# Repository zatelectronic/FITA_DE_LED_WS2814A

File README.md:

<div align="center">

# WS2814A

**Barra de LEDs endereçáveis RGBW com 10 pixels WS2814C — protocolo de 1 fio, encadeável, totalmente SMD, alimentação 5V**

</div>

---

## 📋 Índice

- [WS2814A](#ws2814a)
  - [📋 Índice](#-índice)
  - [Visão Geral](#visão-geral)
  - [Renders 3D](#renders-3d)
  - [Funcionalidades](#funcionalidades)
  - [Arquitetura do Pixel](#arquitetura-do-pixel)
  - [Especificações Técnicas](#especificações-técnicas)
  - [Lista de Materiais](#lista-de-materiais)
  - [Pinagem dos Conectores](#pinagem-dos-conectores)
    - [J1 — Entrada (lado esquerdo)](#j1--entrada-lado-esquerdo)
    - [J2 — Saída (lado direito)](#j2--saída-lado-direito)
  - [Encadeamento de Barras](#encadeamento-de-barras)
  - [Aplicações](#aplicações)
  - [Estrutura do Repositório](#estrutura-do-repositório)
  - [Como Usar](#como-usar)
    - [Conexão básica com Arduino / ESP32](#conexão-básica-com-arduino--esp32)
    - [Exemplo com Adafruit NeoPixel](#exemplo-com-adafruit-neopixel)
  - [Sobre](#sobre)

---

## Visão Geral

**WS2814A** é uma barra de LEDs endereçáveis **RGBW** com **10 pixels** individuais, projetada pela **ZAT ELECTRONIC** utilizando **KiCad 10**. Cada pixel é composto por um controlador **WS2814C** (SMD) e um LED **QBLP679-RGBCW** (RGBW — 4 canais: Vermelho, Verde, Azul e Branco), permitindo controle independente de cor e intensidade por pixel.

A comunicação utiliza o protocolo **single-wire (1 fio)** compatível com a família WS28xx, suportado por bibliotecas com modo RGBW, como a **Adafruit NeoPixel**. A barra possui conector de **entrada (DIN)** e **saída (DOUT)** em ambas as extremidades, permitindo **encadeamento de múltiplas barras** em série com um único pino de dados do microcontrolador.

> 💡 O canal **branco dedicado (W)** do LED QBLP679-RGBCW proporciona iluminação branca de alta qualidade sem mistura de cores RGB, ideal para aplicações de iluminação ambiente e fotografia.

---

## Renders 3D

<div align="center">

*Vista superior — 10 pixels RGBW em série, controladores WS2814C e capacitores de desacoplamento*

<br/>

*Vista isométrica — layout compacto SMD com conectores de entrada e saída nas extremidades*

</div>

---

## Funcionalidades

- ✅ **10 pixels RGBW endereçáveis** — controle individual de cor e brilho por pixel
- ✅ **Controlador WS2814C** (SMD) por pixel — protocolo single-wire compatível com WS28xx
- ✅ **LED QBLP679-RGBCW** por pixel — RGBW com canal branco dedicado (4 canais)
- ✅ **Protocolo 1 fio** — família WS28xx, quadro de 32 bits por pixel (R, G, B, W); compatível com Adafruit NeoPixel (NEO_RGBW)
- ✅ **Encadeável (DIN → DOUT)** — múltiplas barras em série com 1 único pino de dados
- ✅ **Conector de entrada J1** (5V / DIN / GND) — lado esquerdo da barra
- ✅ **Conector de saída J2** (5V / DOUT / GND) — lado direito para encadeamento
- ✅ **Filtro RC no VDD de cada WS2814C** — R1–R10 100 Ω + C1–C10 100 nF (0603 SMD)
- ✅ **3 pontos fiduciais** (FID1–FID3) — referência para montagem SMD automatizada
- ✅ **Alimentação 5VDC** — compatível com fontes USB e reguladores padrão
- ✅ **Layout totalmente SMD** — compacto e adequado para fabricação automatizada

---

## Arquitetura do Pixel

Cada um dos 10 pixels da barra é composto por:

```
   +5V ──[R_n 100Ω]──┬──► VDD  WS2814C (U_n)            +5V
                     │                                    │
               [C_n 100nF]          OUTR ──► K_R ┐        │
                     │              OUTG ──► K_G │ D_n    ├── anodos A_R / A_G / A_B / A_W
                    GND             OUTB ──► K_B │ RGBW   │
                                    OUTW ──► K_W ┘        │
DIN_n ─────────────────────────────► DIN
                                     DOUT ──► DIN do próximo pixel
```

Os pixels são encadeados internamente em série, do U1/D1 ao U10/D10, com o sinal de dados propagando de pixel em pixel até chegar ao conector de saída DOUT.

---

## Especificações Técnicas

| Parâmetro | Valor |
|-----------|-------|
| **Quantidade de pixels** | 10 |
| **Controlador por pixel** | WS2814C (SMD) |
| **LED por pixel** | QBLP679-RGBCW (RGBW — 4 canais) |
| **Canais de cor** | Vermelho, Verde, Azul, Branco |
| **Resolução por canal** | 8 bits (0–255) por cor |
| **Protocolo de dados** | Single-wire — compatível WS28xx |
| **Tensão de alimentação** | 5VDC (WS2814C: 3,7 V a 5,3 V no VDD) |
| **Corrente por canal** | ~16,5 mA (corrente constante do WS2814C) |
| **Consumo máximo** | ~0,66 A em +5V (10 pixels × 4 canais em 100%) |
| **Conector de entrada** | J1 — 3 pinos: GND / DIN / 5V (pino 1 = GND) |
| **Conector de saída** | J2 — 3 pinos: 5V / DOUT / GND |
| **Capacitores** | 100nF / 0603 SMD (1 por pixel, VDD do WS2814C) |
| **Resistores** | 100Ω / 0603 SMD (1 por pixel, série no VDD do WS2814C) |
| **Fiduciais** | 3x (FID1, FID2, FID3) |
| **Ferramenta de Projeto** | KiCad 10 |
| **Tipo de montagem** | SMD — fabricação automatizada (J1/J2 PTH na borda) |
| **Placa** | 150 × 15 mm, 2 camadas |

---

## Lista de Materiais

| Ref | Componente | Valor / Parte | Encapsulamento |
|-----|-----------|--------------|----------------|
| U1–U10 | Controlador LED | WS2814C | SOP-8 (ZAT_LED:ws2814c) |
| D1–D10 | LED RGBW | QBLP679-RGBCW | PLCC-8 (ZAT_LED:QBLP679RGBCW) |
| C1–C10 | Capacitor de desacoplamento | 100nF | 0603 SMD |
| R1–R10 | Resistor do filtro RC do VDD | 100Ω | 0603 SMD |
| J1 | Conector de Entrada | GND / DIN / 5V | Barra de pinos 1x3 90° 2,54 mm, na borda |
| J2 | Conector de Saída | 5V / DOUT / GND | Barra de pinos 1x3 90° 2,54 mm, na borda |
| FID1–FID3 | Fiducial de montagem | — | Fiducial 1mm / Mask 2mm |

---

## Pinagem dos Conectores

### J1 — Entrada (lado esquerdo)

| Pino | Sinal | Descrição |
|------|-------|-----------|
| 1 | GND | Terra |
| 2 | DIN | Entrada de dados serial |
| 3 | 5V | Alimentação positiva |

> J1 e J2 são espelhados: na placa, a linha de cima é sempre 5V e a de baixo GND, para encaixar uma barra na outra.

### J2 — Saída (lado direito)

| Pino | Sinal | Descrição |
|------|-------|-----------|
| 1 | 5V | Alimentação (passthrough) |
| 2 | DOUT | Saída de dados para próxima barra |
| 3 | GND | Terra |

---

## Encadeamento de Barras

A barra suporta encadeamento em série para criar arranjos maiores com um único pino de dados:

```
Microcontrolador
      │
   Pino DIN
      │
  ┌───▼───────────┐      ┌───────────────┐      ┌───────────────┐
  │  WS2814A #1   │      │  WS2814A #2   │      │  WS2814A #3   │
  │  10 pixels    ├─────►│  10 pixels    ├─────►│  10 pixels    │
  │  J1: DIN      │DOUT  │  J1: DIN      │DOUT  │  J1: DIN      │
  └───────────────┘      └───────────────┘      └───────────────┘
   pixels 1–10            pixels 11–20            pixels 21–30

Fonte 5V ──► J1(5V) de cada barra (alimentação independente por barra)
```

> ⚠️ Para encadeamentos longos, conecte a fonte de alimentação 5V diretamente em cada barra — não apenas na primeira. Isso evita quedas de tensão e variações de cor nos pixels mais distantes.

---

## Aplicações

- 💡 **Iluminação ambiente RGBW** — branco de alta qualidade com canal W dedicado
- 🎨 **Painéis e displays de cor** — efeitos visuais com 10 pixels individualmente controláveis
- 📷 **Iluminação para fotografia e vídeo** — temperatura de cor ajustável via R+G+B+W
- 🏠 **Automação residencial** — integração com Home Assistant, ESPHome, MQTT
- 🤖 **Projetos com Arduino e ESP32** — biblioteca Adafruit NeoPixel (modo RGBW)
- 🎭 **Cenografia e decoração** — efeitos de luz programáveis para eventos
- 🔬 **Laboratório e prototipagem** — módulo de iluminação endereçável para experimentos

---

## Estrutura do Repositório

```
FITA_DE_LED_WS2814A/
├── FITA_DE_LED_WS2814A.kicad_pro   # Projeto KiCad 10
├── FITA_DE_LED_WS2814A.kicad_sch   # Esquemático: capa A2 (índice das folhas)
├── PIXELS_1_5.kicad_sch            # Folha 02: pixels 1 a 5
├── PIXELS_6_10.kicad_sch           # Folha 03: pixels 6 a 10
├── CONN.kicad_sch                  # Folha 04: J1 / J2, fiduciais, PWR_FLAG
├── FITA_DE_LED_WS2814A.kicad_pcb   # Layout da PCB (KiCad 10)
├── FITA_DE_LED_WS2814A.kicad_prl   # Configurações locais
├── FITA_DE_LED_WS2814A.kicad_dru   # Regras customizadas (vazio: version 1)
├── Zat_TitleBlock.kicad_wks        # Title block ZAT ELECTRONIC
├── fabrication-toolkit-options.json  # Configurações de fabricação
├── packages3D/                     # Modelos 3D arquivados (referência)
├── imagem_1.png                    # Render 3D superior
├── imagem_2.png                    # Render 3D isométrico
├── LEIA-ME_REVISAO_R01.md          # O que mudou na revisão R01
└── README.md
```

---

## Como Usar

### Conexão básica com Arduino / ESP32

```
Arduino / ESP32        WS2814A — J1
───────────────        ─────────────
GND          ────────► GND
5V           ────────► 5V
Pino digital ────────► DIN
```

### Biblioteca

O WS2814C recebe **32 bits por pixel** (R, G, B, W). A API clássica da FastLED envia 24 bits (RGB), por isso o exemplo usa a **Adafruit NeoPixel** no modo `NEO_RGBW`.

### Exemplo com Adafruit NeoPixel

```cpp
#include <Adafruit_NeoPixel.h>

#define PIN        6
#define NUMPIXELS 10

Adafruit_NeoPixel strip(NUMPIXELS, PIN, NEO_RGBW + NEO_KHZ800);   // WS2814: ordem R G B W

void setup() {
  strip.begin();
  strip.setBrightness(100);
}

void loop() {
  // Canal branco puro (W)
  for (int i = 0; i < NUMPIXELS; i++) {
    strip.setPixelColor(i, strip.Color(0, 0, 0, 255));
  }
  strip.show();
  delay(1000);

  // Vermelho
  for (int i = 0; i < NUMPIXELS; i++) {
    strip.setPixelColor(i, strip.Color(255, 0, 0, 0));
  }
  strip.show();
  delay(1000);
}
```
## Sobre

<div align="center">

Projetado por **ZAT ELECTRONIC**

*WS2814A — Made in Brazil 🇧🇷*

</div>

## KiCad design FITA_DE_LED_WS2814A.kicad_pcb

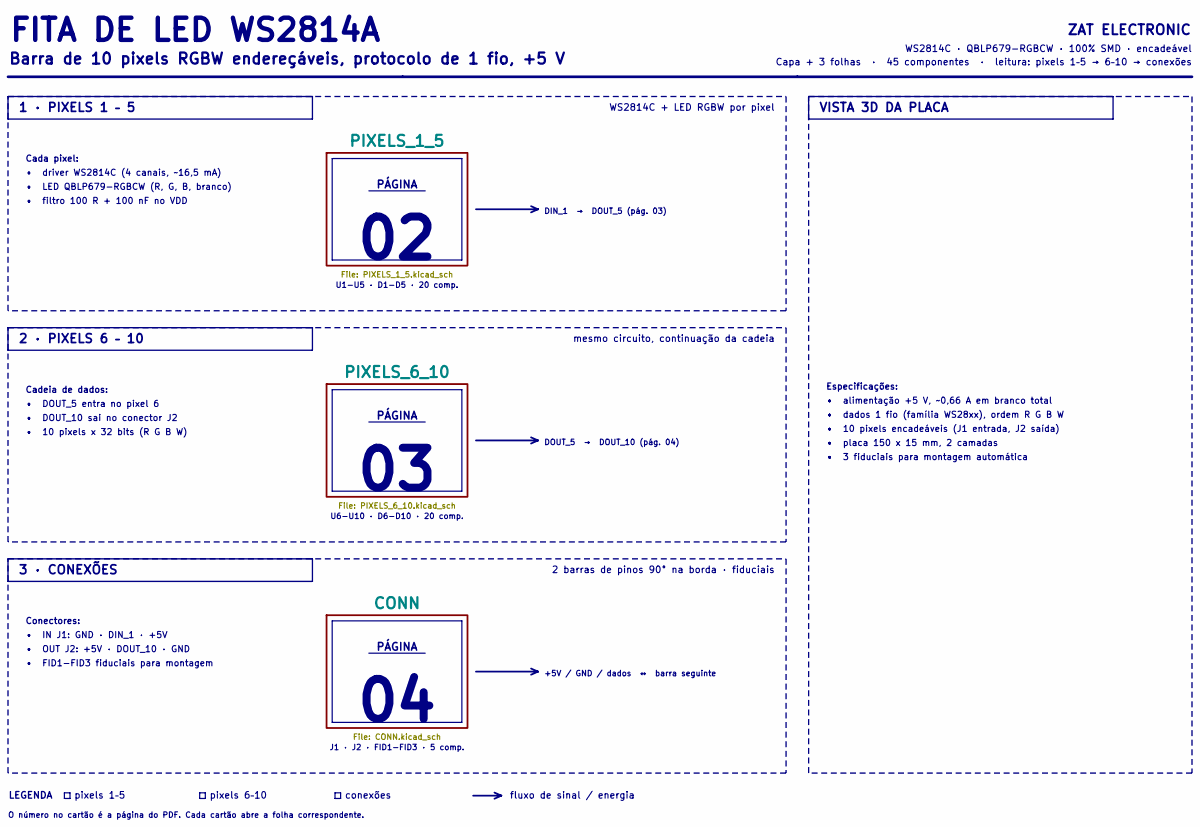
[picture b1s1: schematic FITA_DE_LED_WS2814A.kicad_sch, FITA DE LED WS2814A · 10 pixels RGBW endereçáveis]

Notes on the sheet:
2 barras de pinos 90° na borda · fiduciais
• 10 pixels encadeáveis (J1 entrada, J2 saída)
• LED QBLP679-RGBCW (R, G, B, branco)
• DOUT_5 entra no pixel 6
• placa 150 x 15 mm, 2 camadas
2 · PIXELS 6 – 10
• IN J1: GND · DIN_1 · +5V
Cada pixel:
• DOUT_10 sai no conector J2
• dados 1 fio (família WS28xx), ordem R G B W
• FID1-FID3 fiduciais para montagem
Conectores:
conexões
J1 · J2 · FID1-FID3 · 5 comp.
pixels 6–10
3 · CONEXÕES
O número no cartão é a página do PDF. Cada cartão abre a folha correspondente.
U1-U5 · D1-D5 · 20 comp.
• filtro 100 R + 100 nF no VDD
Capa + 3 folhas · 45 componentes · leitura: pixels 1–5 → 6–10 → conexões
VISTA 3D DA PLACA
PÁGINA
LEGENDA
U6-U10 · D6-D10 · 20 comp.
• 3 fiduciais para montagem automática
DOUT_5 → DOUT_10 (pág. 04)
1 · PIXELS 1 – 5
Cadeia de dados:
ZAT ELECTRONIC
DIN_1 → DOUT_5 (pág. 03)
Especificações:
• alimentação +5 V, ~0,66 A em branco total
• 10 pixels x 32 bits (R G B W)
+5V / GND / dados ↔ barra seguinte
fluxo de sinal / energia
WS2814C + LED RGBW por pixel
pixels 1–5
Barra de 10 pixels RGBW endereçáveis, protocolo de 1 fio, +5 V
WS2814C · QBLP679-RGBCW · 100% SMD · encadeável
mesmo circuito, continuação da cadeia

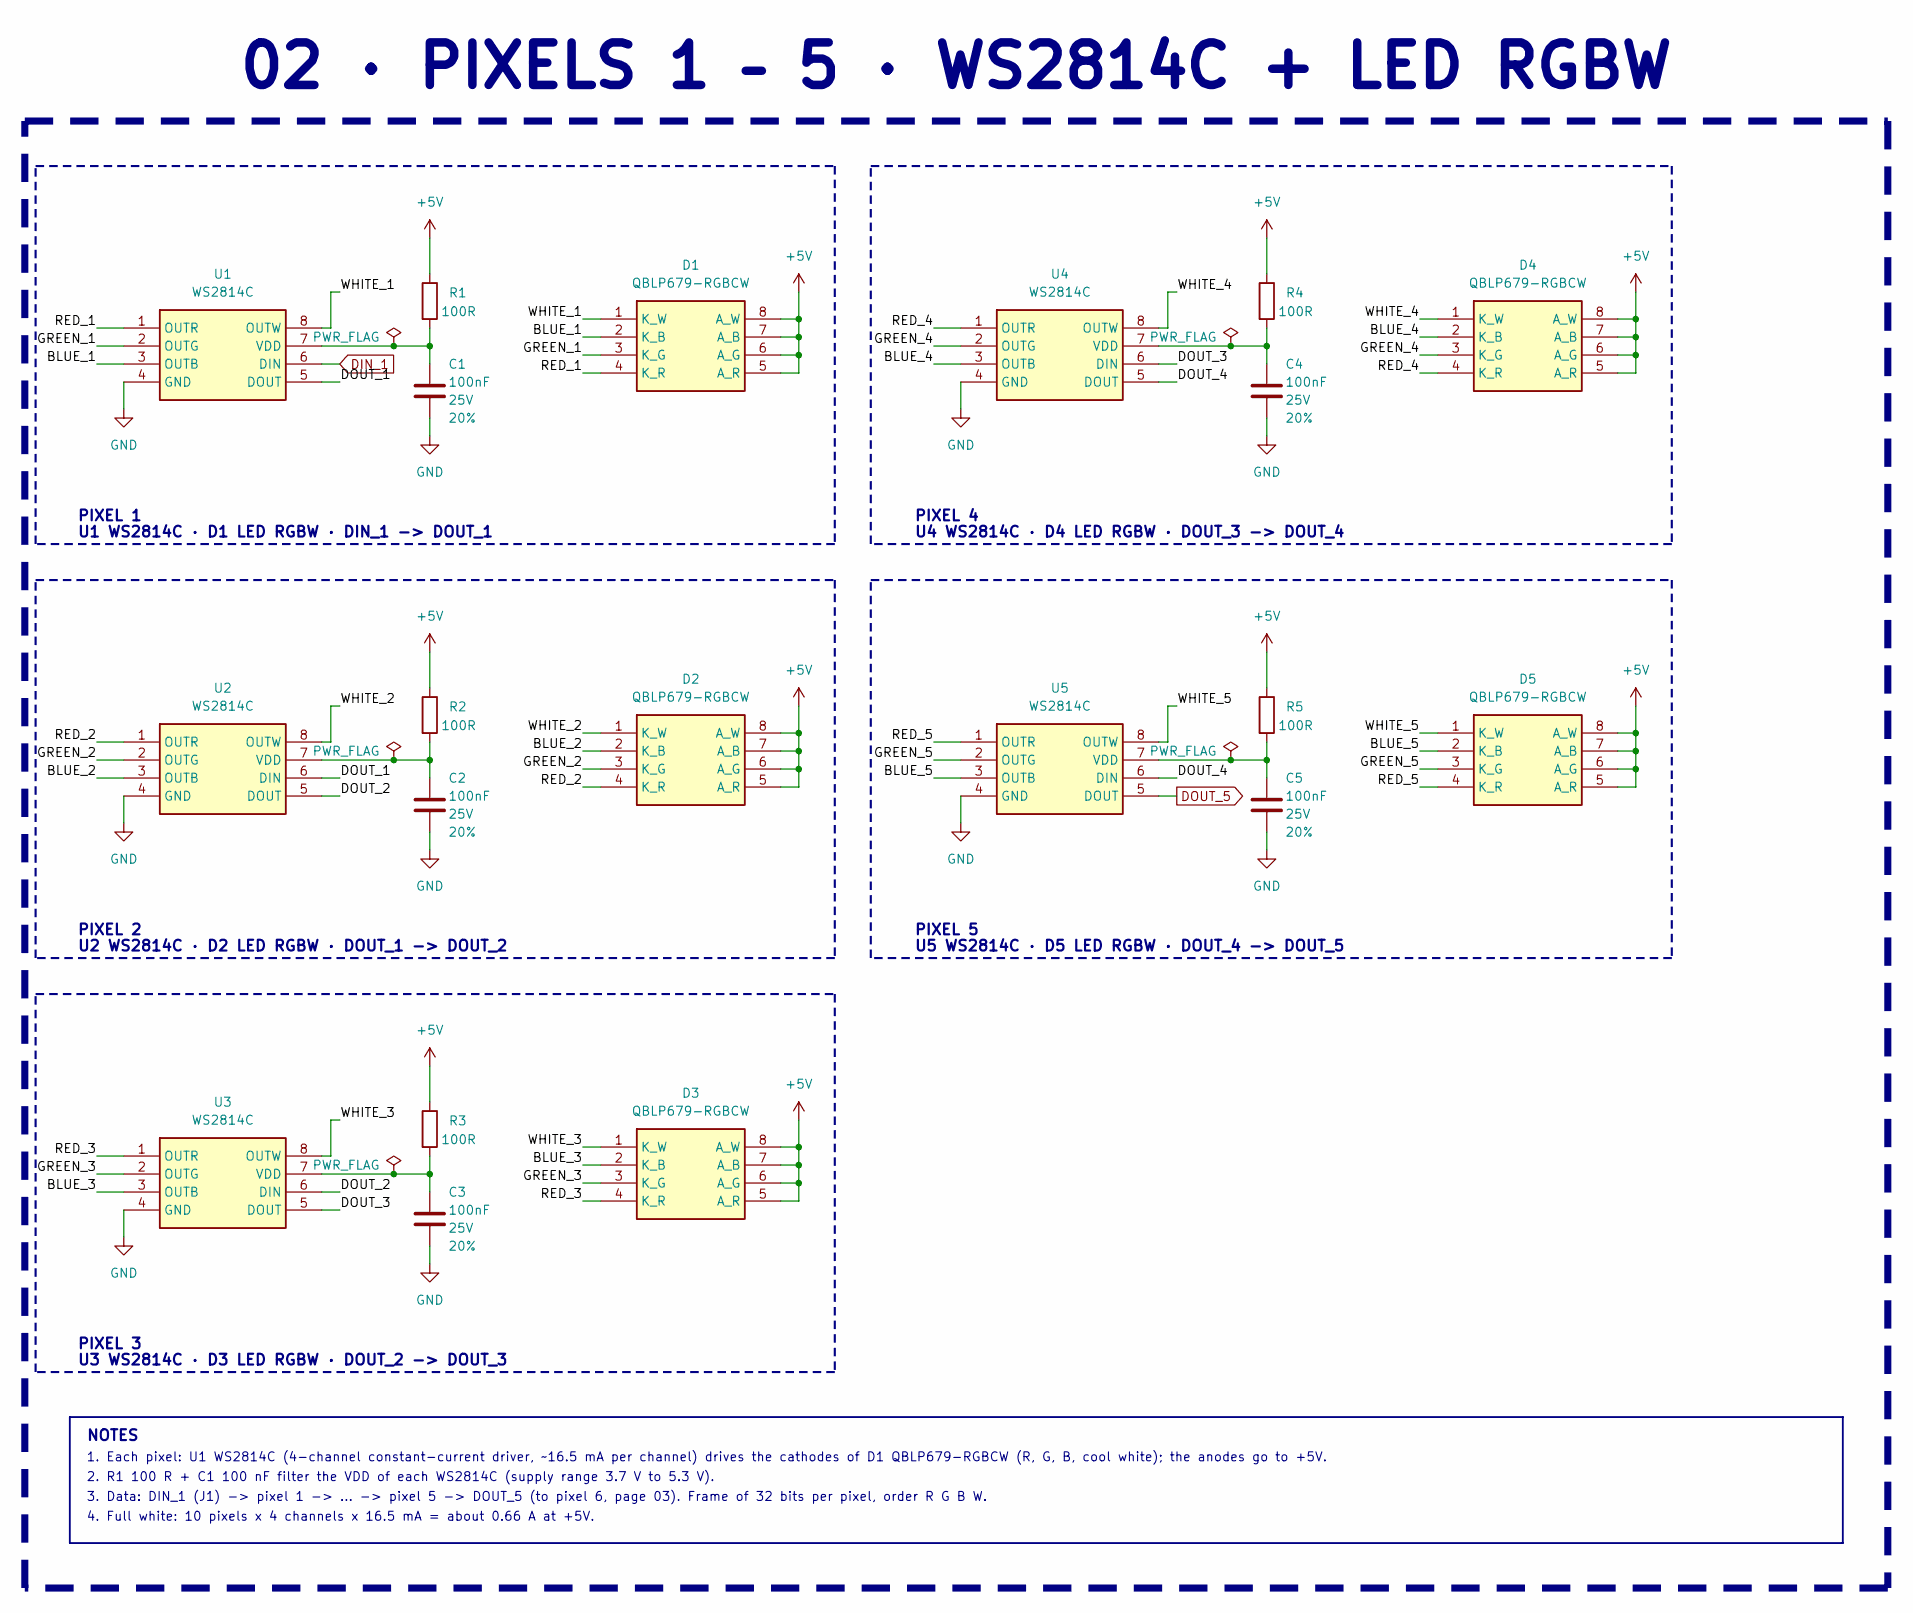
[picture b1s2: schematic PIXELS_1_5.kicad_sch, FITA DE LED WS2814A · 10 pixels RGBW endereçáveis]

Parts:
C1, C2, C3, C4, C5: 100nF; C_0603_1608Metric; Voltage 25V; Tolerance 20%
D1, D2, D3, D4, D5: QBLP679-RGBCW; QBLP679RGBCW; Manufacturer_Part_Number QBLP679-RGBCW
R1, R2, R3, R4, R5: 100R; R_0603_1608Metric; Part Number RC0603FR-07100RL; JLCPCB ID C22775
U1, U2, U3, U4, U5: WS2814C; ws2814c; Manufacturer_Part_Number WS2814C

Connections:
+5V: D1.5 (A_R), D1.6 (A_G), D1.7 (A_B), D1.8 (A_W), D2.5 (A_R), D2.6 (A_G), D2.7 (A_B), D2.8 (A_W), D3.5 (A_R), D3.6 (A_G), D3.7 (A_B), D3.8 (A_W), D4.5 (A_R), D4.6 (A_G), D4.7 (A_B), D4.8 (A_W), D5.5 (A_R), D5.6 (A_G), D5.7 (A_B), D5.8 (A_W), R1.1, R2.1, R3.1, R4.1, R5.1; also elsewhere on the board
/PIXELS_1_5/BLUE_1: D1.2 (K_B), U1.3 (OUTB)
/PIXELS_1_5/BLUE_2: D2.2 (K_B), U2.3 (OUTB)
/PIXELS_1_5/BLUE_3: D3.2 (K_B), U3.3 (OUTB)
/PIXELS_1_5/BLUE_4: D4.2 (K_B), U4.3 (OUTB)
/PIXELS_1_5/BLUE_5: D5.2 (K_B), U5.3 (OUTB)
/PIXELS_1_5/DOUT_1: U1.5 (DOUT), U2.6 (DIN)
/PIXELS_1_5/DOUT_2: U2.5 (DOUT), U3.6 (DIN)
/PIXELS_1_5/DOUT_3: U3.5 (DOUT), U4.6 (DIN)
/PIXELS_1_5/DOUT_4: U4.5 (DOUT), U5.6 (DIN)
/PIXELS_1_5/GREEN_1: D1.3 (K_G), U1.2 (OUTG)
/PIXELS_1_5/GREEN_2: D2.3 (K_G), U2.2 (OUTG)
/PIXELS_1_5/GREEN_3: D3.3 (K_G), U3.2 (OUTG)
/PIXELS_1_5/GREEN_4: D4.3 (K_G), U4.2 (OUTG)
/PIXELS_1_5/GREEN_5: D5.3 (K_G), U5.2 (OUTG)
/PIXELS_1_5/RED_1: D1.4 (K_R), U1.1 (OUTR)
/PIXELS_1_5/RED_2: D2.4 (K_R), U2.1 (OUTR)
/PIXELS_1_5/RED_3: D3.4 (K_R), U3.1 (OUTR)
/PIXELS_1_5/RED_4: D4.4 (K_R), U4.1 (OUTR)
/PIXELS_1_5/RED_5: D5.4 (K_R), U5.1 (OUTR)
/PIXELS_1_5/WHITE_1: D1.1 (K_W), U1.8 (OUTW)
/PIXELS_1_5/WHITE_2: D2.1 (K_W), U2.8 (OUTW)
/PIXELS_1_5/WHITE_3: D3.1 (K_W), U3.8 (OUTW)
/PIXELS_1_5/WHITE_4: D4.1 (K_W), U4.8 (OUTW)
/PIXELS_1_5/WHITE_5: D5.1 (K_W), U5.8 (OUTW)
DIN_1: U1.6 (DIN); also elsewhere on the board
DOUT_5: U5.5 (DOUT); also elsewhere on the board
GND: C1.2, C2.2, C3.2, C4.2, C5.2, U1.4 (GND), U2.4 (GND), U3.4 (GND), U4.4 (GND), U5.4 (GND); also elsewhere on the board
unnamed: C1.1, R1.2, U1.7 (VDD)
unnamed: C2.1, R2.2, U2.7 (VDD)
unnamed: C3.1, R3.2, U3.7 (VDD)
unnamed: C4.1, R4.2, U4.7 (VDD)
unnamed: C5.1, R5.2, U5.7 (VDD)

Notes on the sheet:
PIXEL 4
U4 WS2814C · D4 LED RGBW · DOUT_3 -> DOUT_4
PIXEL 3
PIXEL 1
U3 WS2814C · D3 LED RGBW · DOUT_2 -> DOUT_3
NOTES
02 · PIXELS 1 – 5 · WS2814C + LED RGBW
PIXEL 2
PIXEL 5
4. Full white: 10 pixels x 4 channels x 16.5 mA = about 0.66 A at +5V.
3. Data: DIN_1 (J1) -> pixel 1 -> ... -> pixel 5 -> DOUT_5 (to pixel 6, page 03). Frame of 32 bits per pixel, order R G B W.
1. Each pixel: U1 WS2814C (4-channel constant-current driver, ~16.5 mA per channel) drives the cathodes of D1 QBLP679-RGBCW (R, G, B, cool white); the anodes go to +5V.
2. R1 100 R + C1 100 nF filter the VDD of each WS2814C (supply range 3.7 V to 5.3 V).
U2 WS2814C · D2 LED RGBW · DOUT_1 -> DOUT_2
U1 WS2814C · D1 LED RGBW · DIN_1 -> DOUT_1
U5 WS2814C · D5 LED RGBW · DOUT_4 -> DOUT_5

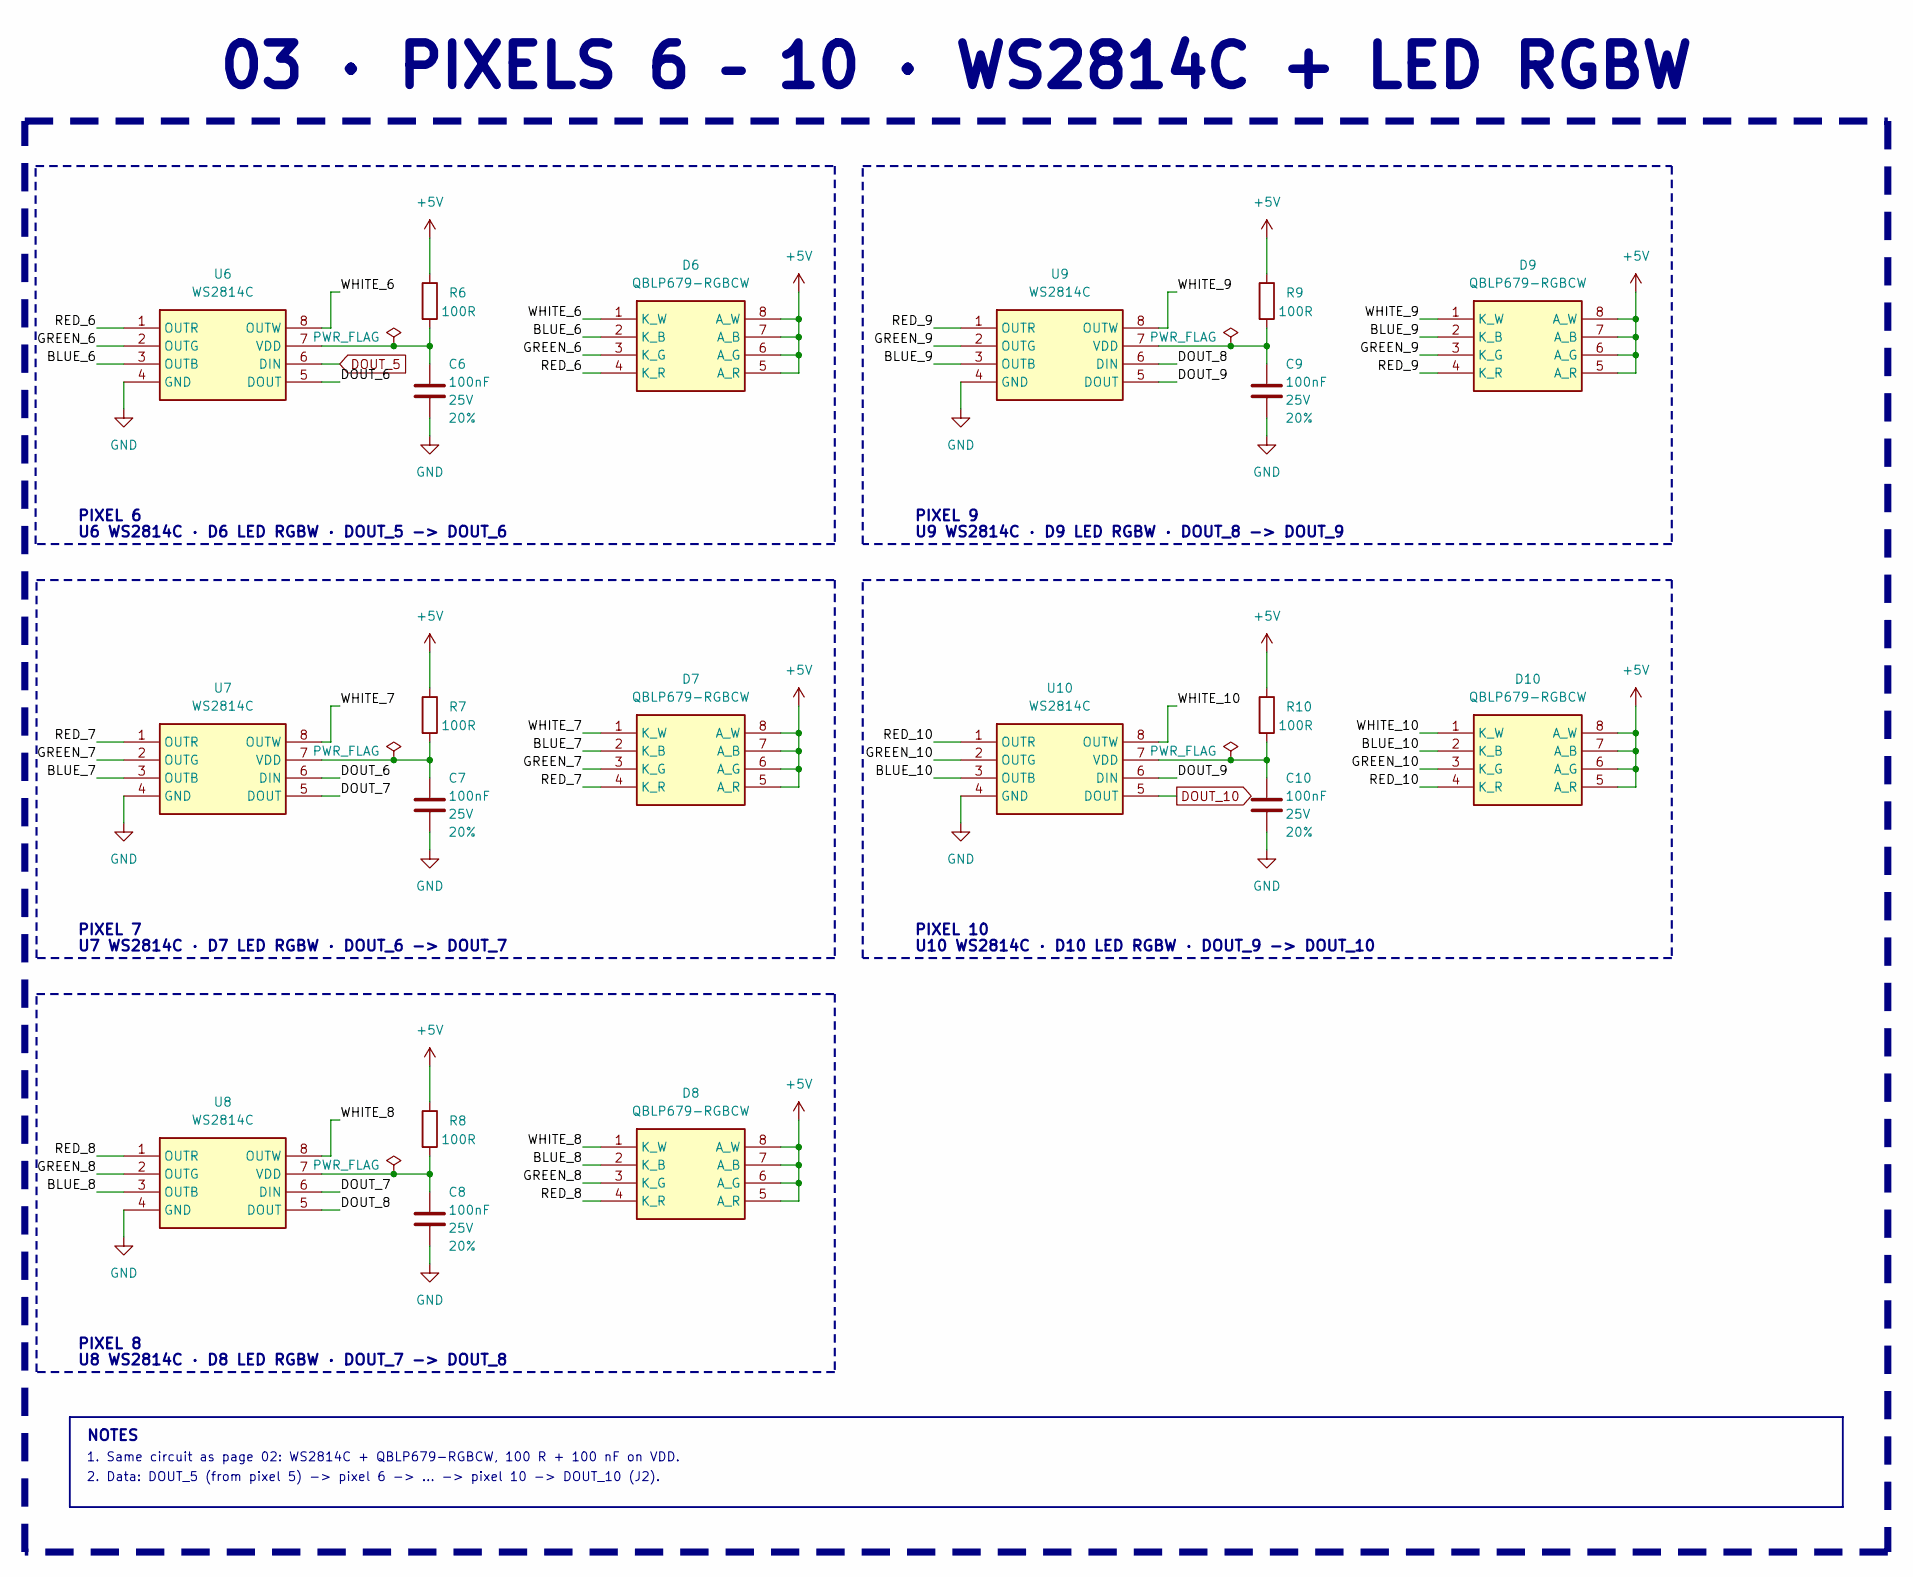
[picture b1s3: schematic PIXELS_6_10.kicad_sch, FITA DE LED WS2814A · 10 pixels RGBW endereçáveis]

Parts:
C6, C7, C8, C9, C10: 100nF; C_0603_1608Metric; Voltage 25V; Tolerance 20%
D6, D7, D8, D9, D10: QBLP679-RGBCW; QBLP679RGBCW; Manufacturer_Part_Number QBLP679-RGBCW
R6, R7, R8, R9, R10: 100R; R_0603_1608Metric; Part Number RC0603FR-07100RL; JLCPCB ID C22775
U6, U7, U8, U9, U10: WS2814C; ws2814c; Manufacturer_Part_Number WS2814C

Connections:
+5V: D6.5 (A_R), D6.6 (A_G), D6.7 (A_B), D6.8 (A_W), D7.5 (A_R), D7.6 (A_G), D7.7 (A_B), D7.8 (A_W), D8.5 (A_R), D8.6 (A_G), D8.7 (A_B), D8.8 (A_W), D9.5 (A_R), D9.6 (A_G), D9.7 (A_B), D9.8 (A_W), D10.5 (A_R), D10.6 (A_G), D10.7 (A_B), D10.8 (A_W), R6.1, R7.1, R8.1, R9.1, R10.1; also elsewhere on the board
/PIXELS_6_10/BLUE_6: D6.2 (K_B), U6.3 (OUTB)
/PIXELS_6_10/BLUE_7: D7.2 (K_B), U7.3 (OUTB)
/PIXELS_6_10/BLUE_8: D8.2 (K_B), U8.3 (OUTB)
/PIXELS_6_10/BLUE_9: D9.2 (K_B), U9.3 (OUTB)
/PIXELS_6_10/BLUE_10: D10.2 (K_B), U10.3 (OUTB)
/PIXELS_6_10/DOUT_6: U6.5 (DOUT), U7.6 (DIN)
/PIXELS_6_10/DOUT_7: U7.5 (DOUT), U8.6 (DIN)
/PIXELS_6_10/DOUT_8: U8.5 (DOUT), U9.6 (DIN)
/PIXELS_6_10/DOUT_9: U9.5 (DOUT), U10.6 (DIN)
/PIXELS_6_10/GREEN_6: D6.3 (K_G), U6.2 (OUTG)
/PIXELS_6_10/GREEN_7: D7.3 (K_G), U7.2 (OUTG)
/PIXELS_6_10/GREEN_8: D8.3 (K_G), U8.2 (OUTG)
/PIXELS_6_10/GREEN_9: D9.3 (K_G), U9.2 (OUTG)
/PIXELS_6_10/GREEN_10: D10.3 (K_G), U10.2 (OUTG)
/PIXELS_6_10/RED_6: D6.4 (K_R), U6.1 (OUTR)
/PIXELS_6_10/RED_7: D7.4 (K_R), U7.1 (OUTR)
/PIXELS_6_10/RED_8: D8.4 (K_R), U8.1 (OUTR)
/PIXELS_6_10/RED_9: D9.4 (K_R), U9.1 (OUTR)
/PIXELS_6_10/RED_10: D10.4 (K_R), U10.1 (OUTR)
/PIXELS_6_10/WHITE_6: D6.1 (K_W), U6.8 (OUTW)
/PIXELS_6_10/WHITE_7: D7.1 (K_W), U7.8 (OUTW)
/PIXELS_6_10/WHITE_8: D8.1 (K_W), U8.8 (OUTW)
/PIXELS_6_10/WHITE_9: D9.1 (K_W), U9.8 (OUTW)
/PIXELS_6_10/WHITE_10: D10.1 (K_W), U10.8 (OUTW)
DOUT_5: U6.6 (DIN); also elsewhere on the board
DOUT_10: U10.5 (DOUT); also elsewhere on the board
GND: C6.2, C7.2, C8.2, C9.2, C10.2, U6.4 (GND), U7.4 (GND), U8.4 (GND), U9.4 (GND), U10.4 (GND); also elsewhere on the board
unnamed: C6.1, R6.2, U6.7 (VDD)
unnamed: C7.1, R7.2, U7.7 (VDD)
unnamed: C8.1, R8.2, U8.7 (VDD)
unnamed: C9.1, R9.2, U9.7 (VDD)
unnamed: C10.1, R10.2, U10.7 (VDD)

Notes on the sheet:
U10 WS2814C · D10 LED RGBW · DOUT_9 -> DOUT_10
PIXEL 7
U9 WS2814C · D9 LED RGBW · DOUT_8 -> DOUT_9
U6 WS2814C · D6 LED RGBW · DOUT_5 -> DOUT_6
U7 WS2814C · D7 LED RGBW · DOUT_6 -> DOUT_7
2. Data: DOUT_5 (from pixel 5) -> pixel 6 -> ... -> pixel 10 -> DOUT_10 (J2).
PIXEL 6
PIXEL 9
1. Same circuit as page 02: WS2814C + QBLP679-RGBCW, 100 R + 100 nF on VDD.
PIXEL 8
PIXEL 10
03 · PIXELS 6 – 10 · WS2814C + LED RGBW
U8 WS2814C · D8 LED RGBW · DOUT_7 -> DOUT_8
NOTES

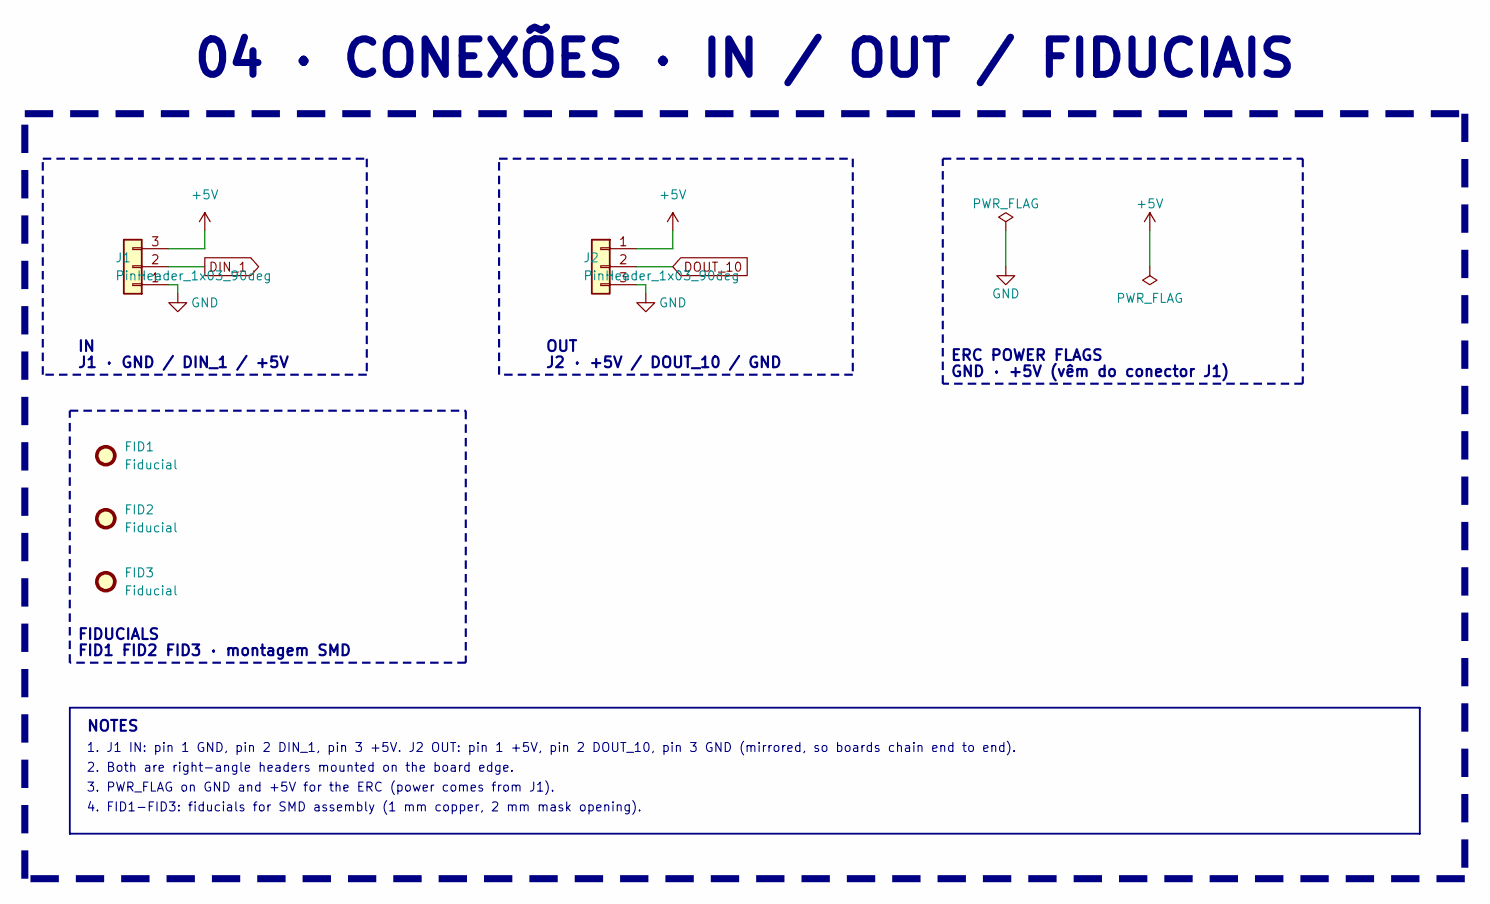
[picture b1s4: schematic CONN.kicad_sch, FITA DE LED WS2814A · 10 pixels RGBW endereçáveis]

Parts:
FID1, FID2, FID3: Fiducial; Fiducial_1mm_Mask2mm
J1, J2: PinHeader_1x03_90deg; PinHeader_1x03_P2.54mm_Horizontal_EdgeMount

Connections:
+5V: J1.3, J2.1; also elsewhere on the board
DIN_1: J1.2; also elsewhere on the board
DOUT_10: J2.2; also elsewhere on the board
GND: J1.1, J2.3; also elsewhere on the board

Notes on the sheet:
J1 · GND / DIN_1 / +5V
2. Both are right-angle headers mounted on the board edge.
ERC POWER FLAGS
1. J1 IN: pin 1 GND, pin 2 DIN_1, pin 3 +5V. J2 OUT: pin 1 +5V, pin 2 DOUT_10, pin 3 GND (mirrored, so boards chain end to end).
J2 · +5V / DOUT_10 / GND
4. FID1-FID3: fiducials for SMD assembly (1 mm copper, 2 mm mask opening).
FIDUCIALS
04 · CONEXÕES · IN / OUT / FIDUCIAIS
3. PWR_FLAG on GND and +5V for the ERC (power comes from J1).
OUT
GND · +5V (vêm do conector J1)
NOTES
FID1 FID2 FID3 · montagem SMD

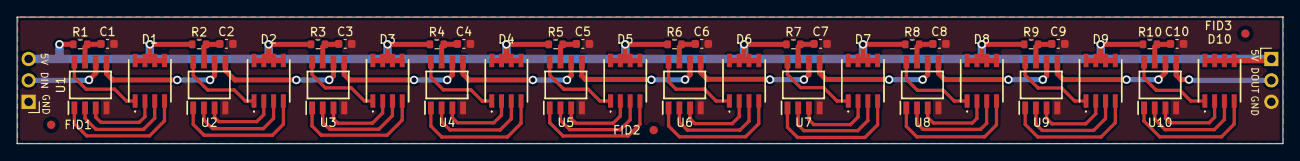
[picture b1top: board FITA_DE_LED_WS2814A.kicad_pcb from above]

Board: 2 copper layers, 150.0 x 15.0 mm, 45 parts (0 on the bottom side), 63 nets.

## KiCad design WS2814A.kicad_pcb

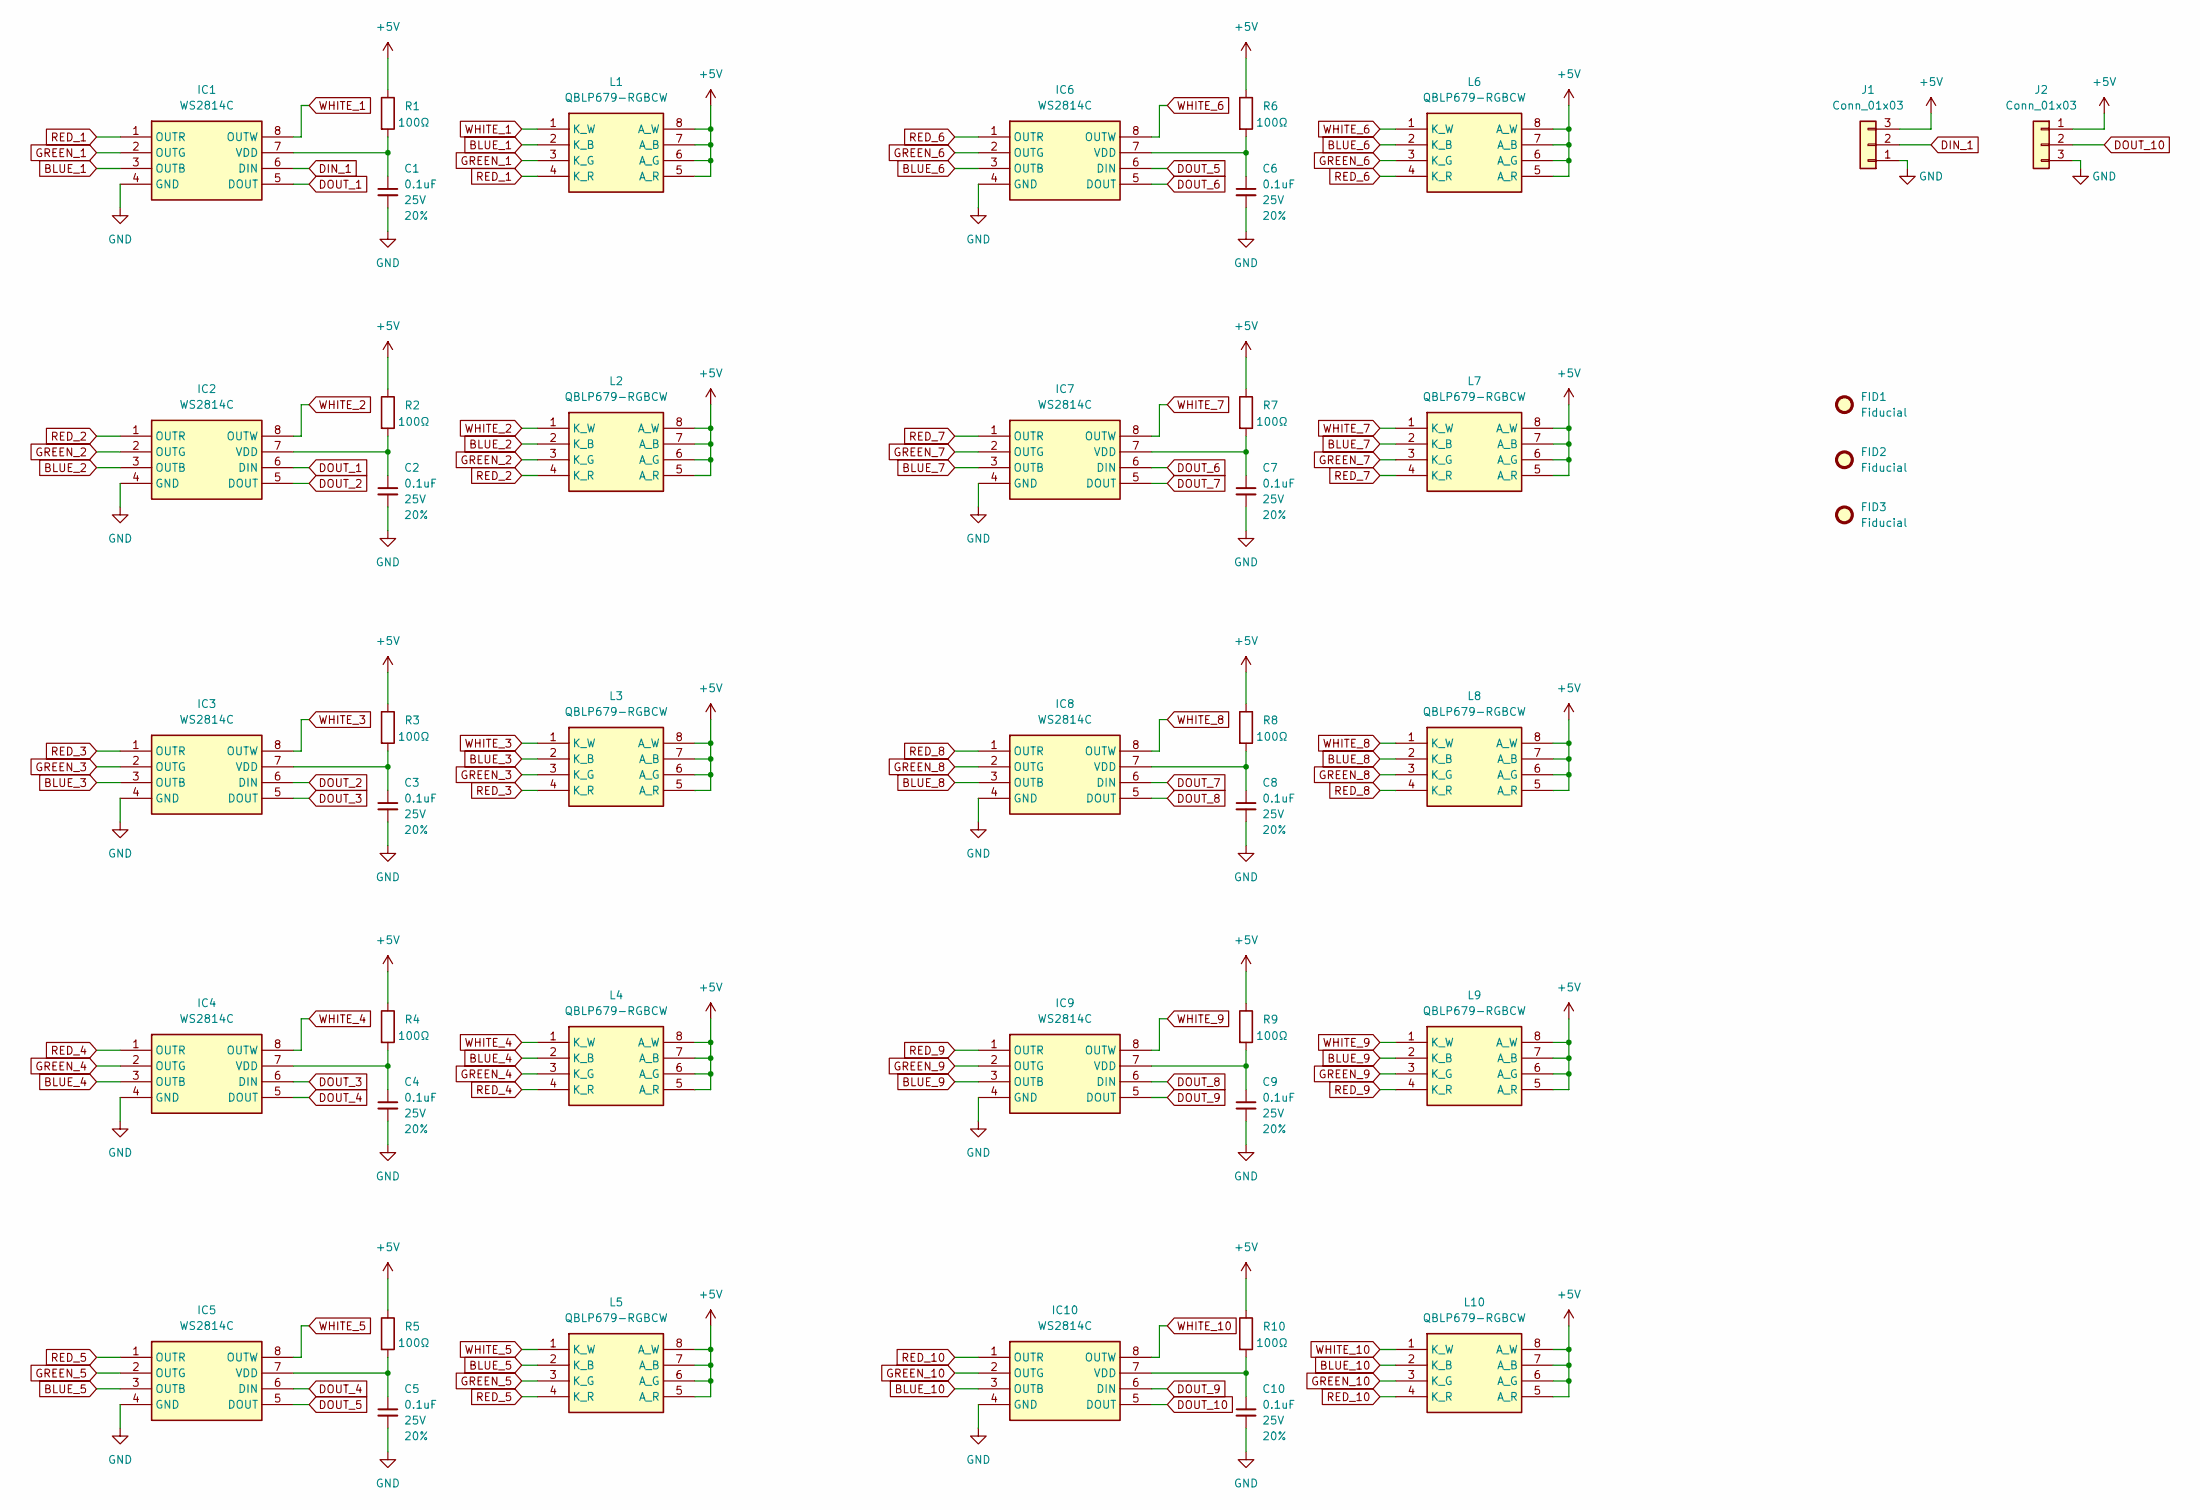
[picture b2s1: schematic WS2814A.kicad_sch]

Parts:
C1, C2, C3, C4, C5, C6, C7, C8, C9, C10: 0.1uF; C_0603; Voltage 25V; Tolerance 20%
FID1, FID2, FID3: Fiducial; Fiducial_1mm_Mask2mm
IC1, IC2, IC3, IC4, IC5, IC6, IC7, IC8, IC9, IC10: WS2814C; ws2814c; Manufacturer_Part_Number WS2814C
J1, J2: Conn_01x03; PinHeader_1x03_P2.54mm_Horizontal
L1, L2, L3, L4, L5, L6, L7, L8, L9, L10: QBLP679-RGBCW; QBLP679RGBCW; Manufacturer_Part_Number QBLP679-RGBCW
R1, R2, R3, R4, R5, R6, R7, R8, R9, R10: 100_0603; R_0603; Part Number RC0603FR-07100RL; JLCPCB ID C22775

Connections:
+5V: J1.3, J2.1, L1.5 (A_R), L1.6 (A_G), L1.7 (A_B), L1.8 (A_W), L2.5 (A_R), L2.6 (A_G), L2.7 (A_B), L2.8 (A_W), L3.5 (A_R), L3.6 (A_G), L3.7 (A_B), L3.8 (A_W), L4.5 (A_R), L4.6 (A_G), L4.7 (A_B), L4.8 (A_W), L5.5 (A_R), L5.6 (A_G), L5.7 (A_B), L5.8 (A_W), L6.5 (A_R), L6.6 (A_G), L6.7 (A_B), L6.8 (A_W), L7.5 (A_R), L7.6 (A_G), L7.7 (A_B), L7.8 (A_W), L8.5 (A_R), L8.6 (A_G), L8.7 (A_B), L8.8 (A_W), L9.5 (A_R), L9.6 (A_G), L9.7 (A_B), L9.8 (A_W), L10.5 (A_R), L10.6 (A_G), L10.7 (A_B), L10.8 (A_W), R1.1, R2.1, R3.1, R4.1, R5.1, R6.1, R7.1, R8.1, R9.1, R10.1
BLUE_1: IC1.3 (OUTB), L1.2 (K_B)
BLUE_2: IC2.3 (OUTB), L2.2 (K_B)
BLUE_3: IC3.3 (OUTB), L3.2 (K_B)
BLUE_4: IC4.3 (OUTB), L4.2 (K_B)
BLUE_5: IC5.3 (OUTB), L5.2 (K_B)
BLUE_6: IC6.3 (OUTB), L6.2 (K_B)
BLUE_7: IC7.3 (OUTB), L7.2 (K_B)
BLUE_8: IC8.3 (OUTB), L8.2 (K_B)
BLUE_9: IC9.3 (OUTB), L9.2 (K_B)
BLUE_10: IC10.3 (OUTB), L10.2 (K_B)
DIN_1: IC1.6 (DIN), J1.2
DOUT_1: IC1.5 (DOUT), IC2.6 (DIN)
DOUT_2: IC2.5 (DOUT), IC3.6 (DIN)
DOUT_3: IC3.5 (DOUT), IC4.6 (DIN)
DOUT_4: IC4.5 (DOUT), IC5.6 (DIN)
DOUT_5: IC5.5 (DOUT), IC6.6 (DIN)
DOUT_6: IC6.5 (DOUT), IC7.6 (DIN)
DOUT_7: IC7.5 (DOUT), IC8.6 (DIN)
DOUT_8: IC8.5 (DOUT), IC9.6 (DIN)
DOUT_9: IC9.5 (DOUT), IC10.6 (DIN)
DOUT_10: IC10.5 (DOUT), J2.2
GND: C1.2, C2.2, C3.2, C4.2, C5.2, C6.2, C7.2, C8.2, C9.2, C10.2, IC1.4 (GND), IC2.4 (GND), IC3.4 (GND), IC4.4 (GND), IC5.4 (GND), IC6.4 (GND), IC7.4 (GND), IC8.4 (GND), IC9.4 (GND), IC10.4 (GND), J1.1, J2.3
GREEN_1: IC1.2 (OUTG), L1.3 (K_G)
GREEN_2: IC2.2 (OUTG), L2.3 (K_G)
GREEN_3: IC3.2 (OUTG), L3.3 (K_G)
GREEN_4: IC4.2 (OUTG), L4.3 (K_G)
GREEN_5: IC5.2 (OUTG), L5.3 (K_G)
GREEN_6: IC6.2 (OUTG), L6.3 (K_G)
GREEN_7: IC7.2 (OUTG), L7.3 (K_G)
GREEN_8: IC8.2 (OUTG), L8.3 (K_G)
GREEN_9: IC9.2 (OUTG), L9.3 (K_G)
GREEN_10: IC10.2 (OUTG), L10.3 (K_G)
unnamed: C1.1, IC1.7 (VDD), R1.2
unnamed: C2.1, IC2.7 (VDD), R2.2
unnamed: C3.1, IC3.7 (VDD), R3.2
unnamed: C4.1, IC4.7 (VDD), R4.2
unnamed: C5.1, IC5.7 (VDD), R5.2
unnamed: C6.1, IC6.7 (VDD), R6.2
unnamed: C7.1, IC7.7 (VDD), R7.2
unnamed: C8.1, IC8.7 (VDD), R8.2
unnamed: C9.1, IC9.7 (VDD), R9.2
unnamed: C10.1, IC10.7 (VDD), R10.2
RED_1: IC1.1 (OUTR), L1.4 (K_R)
RED_2: IC2.1 (OUTR), L2.4 (K_R)
RED_3: IC3.1 (OUTR), L3.4 (K_R)
RED_4: IC4.1 (OUTR), L4.4 (K_R)
RED_5: IC5.1 (OUTR), L5.4 (K_R)
RED_6: IC6.1 (OUTR), L6.4 (K_R)
RED_7: IC7.1 (OUTR), L7.4 (K_R)
RED_8: IC8.1 (OUTR), L8.4 (K_R)
RED_9: IC9.1 (OUTR), L9.4 (K_R)
RED_10: IC10.1 (OUTR), L10.4 (K_R)
WHITE_1: IC1.8 (OUTW), L1.1 (K_W)
WHITE_2: IC2.8 (OUTW), L2.1 (K_W)
WHITE_3: IC3.8 (OUTW), L3.1 (K_W)
WHITE_4: IC4.8 (OUTW), L4.1 (K_W)
WHITE_5: IC5.8 (OUTW), L5.1 (K_W)
WHITE_6: IC6.8 (OUTW), L6.1 (K_W)
WHITE_7: IC7.8 (OUTW), L7.1 (K_W)
WHITE_8: IC8.8 (OUTW), L8.1 (K_W)
WHITE_9: IC9.8 (OUTW), L9.1 (K_W)
WHITE_10: IC10.8 (OUTW), L10.1 (K_W)

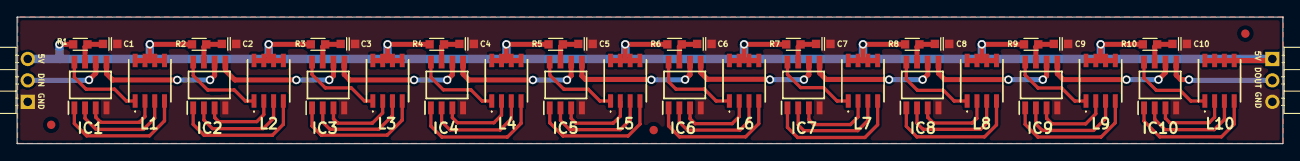
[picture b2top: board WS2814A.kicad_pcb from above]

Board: 2 copper layers, 150.0 x 15.0 mm, 45 parts (0 on the bottom side), 63 nets.

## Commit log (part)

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2026-06-28 COMMIT-28-06-2026
2026-06-28 commit_3
2026-06-29 COMMIT-4
2026-06-29 COMMIT-5
